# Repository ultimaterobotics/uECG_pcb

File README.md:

## uECG PCB version 4.52
 Changelog:

- Replaced AD8606 op amp with a pair of TLV271s;
- LDOs (3.3V for digital, 3V for analog side) were mixed in the previous version; strangely this didn’t affect functioning, but now this is fixed;
- Replaced BMI160 with LSM6DS3TR-C;
- Changed C6 capacitor from 2.2uF to 10uF for better low frequency performance;
- Replaced circuit protection (red LED) with diodes for more reliability;
- Changed charge resistor to 8.2K Ohm to fit the battery charging better;
- Replaced MCP71831 charger IC with TP4054; 
- Added thermistor for measuring temperature;
- Changed RGB LED to different part number;
- Added Ultimate Robotics logo on the back of the PCB.

## uECG device PCB version 4.5

PCB design in KiCAD. The main difference vs previous versions is that power is controlled via button, and slider switch is used only for long storage / shipping (and also to reset the firmware if something went really wrong).

Main project repository: https://github.com/ultimaterobotics/uECG

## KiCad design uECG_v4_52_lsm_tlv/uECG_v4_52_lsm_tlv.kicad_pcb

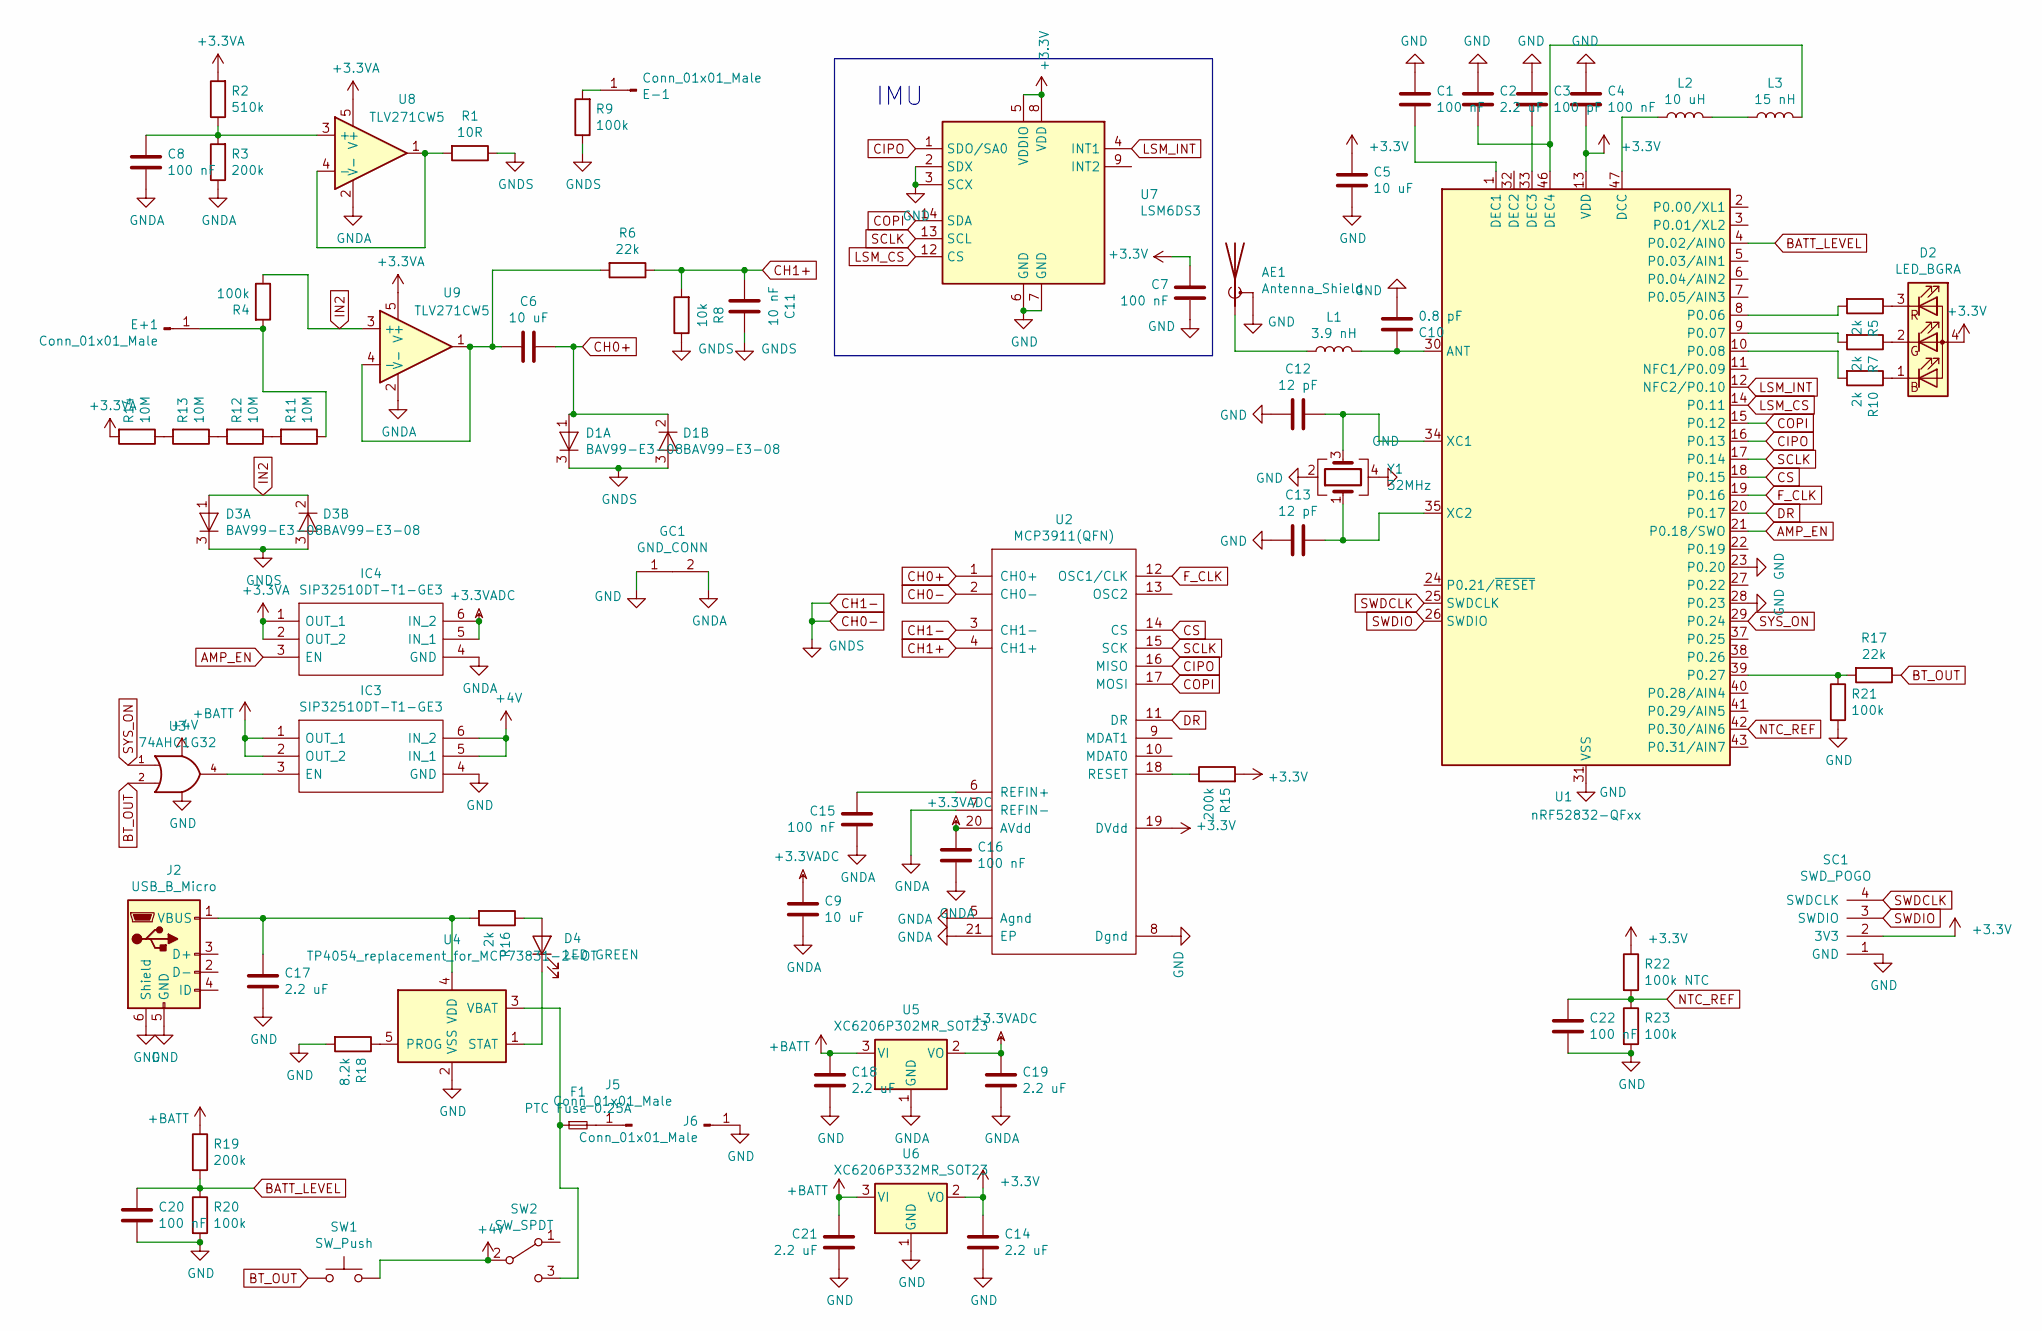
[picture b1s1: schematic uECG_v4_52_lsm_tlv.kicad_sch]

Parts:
AE1: Antenna_Shield; U.FL_Hirose_U.FL-R-SMT-1_Vertical; JLCPN C88373
C1, C4, C7, C8, C15, C16, C20, C22: 100 nF; C_0402_1005Metric; JLCPN C1525
C2, C14, C17, C18, C19, C21: 2.2 uF; C_0402_1005Metric; JLCPN C12530
C3: 100 pF; C_0402_1005Metric; JLCPN C106200
C5, C6, C9: 10 uF; C_0402_1005Metric; JLCPN C315248
C10: 0.8 pF; C_0402_1005Metric; JLCPN C88902
C11: 10 nF; C_0402_1005Metric; JLCPN C15195
C12, C13: 12 pF; C_0402_1005Metric; JLCPN C1547
D1, D3: BAV99-E3-08; SOT-23; JLCPN C2500
D2: LED_BGRA; LED_RGB_0603_a4; JLCPN C282128
D4: LED GREEN; LED_0603_1608Metric; JLCPN C72043
E+1: Conn_01x01_Male; PinHeader_1x01_P2.54mm_Vertical
E-1: Conn_01x01_Male; PinHeader_1x01_P2.54mm_Vertical
F1: PTC Fuse 0.25A; Fuse_0603_1608Metric; JLCPN C207011
GC1: GND_CONN
IC3, IC4: SIP32510DT-T1-GE3; TSOT-23-6; Manufacturer_Part_Number SIP32509DT-T1-GE3; JLCPN C145264
J2: USB_B_Micro; conn_usb_B_micro_smd_our
J5: Conn_01x01_Male; Pin_Header_Straight_1x01_Pitch2.54mm
J6: Conn_01x01_Male; PinHeader_1x01_P2.54mm_Vertical
L1: 3.9 nH; L_0402_1005Metric; JLCPN C14033
L2: 10 uH; L_0603_1608Metric; JLCPN C51942
L3: 15 nH; L_0402_1005Metric; JLCPN C27143
R1: 10R; R_0402_1005Metric; JLCPN C25077
R2: 510k; R_0402_1005Metric; JLCPN C11616
R3, R15, R19: 200k; R_0402_1005Metric; JLCPN C25764
R4, R9, R20, R21, R23: 100k; R_0402_1005Metric; JLCPN C25741
R5, R7, R10, R16: 2k; R_0402_1005Metric; JLCPN C4109
R6, R17: 22k; R_0402_1005Metric; JLCPN C25768
R8: 10k; R_0402_1005Metric; JLCPN C25744
R11, R12, R13, R14: 10М; R_0402_1005Metric; JLCPN C26082
R18: 8.2k; R_0402_1005Metric; JLCPN C25924
R22: 100k NTC; R_0402_1005Metric; JLCPN C77130
SC1: SWD_POGO
SW1: SW_Push; BTN_HY_1185
SW2: SW_SPDT; SW_SPDT_PCM12
U1: nRF52832-QFxx; QFN-48-1EP_6x6mm_Pitch0.4mm; JLCPN C77540
U2: MCP3911(QFN); QFN-20-1EP_4x4mm_P0.5mm_EP2.5x2.5mm
U3: 74AHC1G32; SOT-23-5; JLCPN C7470
U4: TP4054_replacement_for_MCP73831-2-OT; SOT-23-5; JLCPN C32574
U5: XC6206P302MR_SOT23; SOT-23; JLCPN C9972
U6: XC6206P332MR_SOT23; SOT-23; JLCPN C5446
U7: LSM6DS3; LGA-14_3x2.5mm_P0.5mm_LayoutBorder3x4y; JLCPN C967633
U8, U9: TLV271CW5; SOT-23-5; JLCPN C150498
Y1: 32MHz; Crystal_SMD_2016-4Pin_2.0x1.6mm; JLCPN C843260

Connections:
+3.3VA: IC4.1 (OUT_1), IC4.2 (OUT_2), R2.2, R14.2, U8.5 (V+), U9.5 (V+)
+3.3VADC: C9.2, C16.2, C19.2, IC4.5 (IN_1), IC4.6 (IN_2), U2.20 (AVdd), U5.2 (VO)
+3V3: C4.1, C5.2, C7.2, C14.2, D2.4 (A), R15.2, R22.1, SC1.2 (3V3), U1.13 (VDD), U1.36 (VDD), U1.48 (VDD), U2.19 (DVdd), U6.2 (VO), U7.5 (VDDIO), U7.8 (VDD)
+4V: IC3.5 (IN_1), IC3.6 (IN_2), SW1.2, SW2.2 (B), U3.5 (VCC)
+BATT: C18.2, C21.2, IC3.1 (OUT_1), IC3.2 (OUT_2), R19.1, U5.3 (VI), U6.3 (VI)
AMP_EN: IC4.3 (EN), U1.21 (P0.18/SWO)
BATT_LEVEL: C20.2, R19.2, R20.1, U1.4 (P0.02/AIN0)
BT_OUT: R17.1, SW1.1, U3.2
CH0+: C6.2, D1.1 (A), D1.2 (K), U2.1 (CH0+)
CH0-: C11.2, D1.3 (A), D3.3 (A), R1.1, R8.1, R9.1, U2.2 (CH0-), U2.3 (CH1-)
CH1+: C11.1, R6.1, R8.2, U2.4 (CH1+)
CIPO: U1.16 (P0.13), U2.16 (MISO), U7.1 (SDO/SA0)
COPI: U1.15 (P0.12), U2.17 (MOSI), U7.14 (SDA)
CS: U1.18 (P0.15), U2.14 (CS)
DR: U1.20 (P0.17), U2.11 (DR)
F_CLK: U1.19 (P0.16), U2.12 (OSC1/CLK)
GND: AE1.2 (Shield), C1.2, C2.2, C3.2, C4.2, C5.1, C7.1, C10.2, C12.1, C13.1, C14.1, C17.1, C18.1, C20.1, C21.1, C22.1, GC1.1, IC3.4 (GND), J2.5 (GND), J2.6 (Shield), J6.1, R18.2, R20.2, R21.2, R23.2, SC1.1 (GND), U1.23 (P0.20), U1.28 (P0.23), U1.31 (VSS), U1.45 (VSS), U1.49 (VSS), U2.8 (Dgnd), U3.3 (GND), U4.2 (VSS), U6.1 (GND), U7.2 (SDX), U7.3 (SCX), U7.6 (GND), U7.7 (GND), Y1.2, Y1.4
GNDA: C8.1, C9.1, C15.1, C16.1, C19.1, GC1.2, IC4.4 (GND), R3.1, U2.5 (Agnd), U2.7 (REFIN-), U2.21 (EP), U5.1 (GND), U8.2 (V-), U9.2 (V-)
IN2: D3.1 (A), D3.2 (K), R4.1, U9.3 (+)
LSM_CS: U1.14 (P0.11), U7.12 (CS)
LSM_INT: U1.12 (NFC2/P0.10), U7.4 (INT1)
NTC_REF: C22.2, R22.2, R23.1, U1.42 (P0.30/AIN6)
unnamed: AE1.1 (A), L1.1
unnamed: C1.1, U1.1 (DEC1)
unnamed: C2.1, L3.2, U1.46 (DEC4)
unnamed: C3.1, U1.33 (DEC3)
unnamed: C6.1, R6.2, U9.1, U9.4 (-)
unnamed: C8.2, R2.1, R3.2, U8.3 (+)
unnamed: C10.1, L1.2, U1.30 (ANT)
unnamed: C12.2, U1.34 (XC1), Y1.3
unnamed: C13.2, U1.35 (XC2), Y1.1
unnamed: C15.2, U2.6 (REFIN+)
unnamed: C17.2, J2.1 (VBUS), R16.2, U4.4 (VDD)
unnamed: D2.1 (BK), R10.1
unnamed: D2.2 (GK), R7.1
unnamed: D2.3 (RK), R5.1
unnamed: D4.1 (K), U4.1 (STAT)
unnamed: D4.2 (A), R16.1
unnamed: E+1.1, R4.2, R11.1
unnamed: E-1.1, R9.2
unnamed: F1.1, SW2.3 (C), U4.3 (VBAT)
unnamed: F1.2, J5.1
unnamed: IC3.3 (EN), U3.4
unnamed: L2.1, U1.47 (DCC)
unnamed: L2.2, L3.1
unnamed: R1.2, U8.1, U8.4 (-)
unnamed: R5.2, U1.8 (P0.06)
unnamed: R7.2, U1.9 (P0.07)
unnamed: R10.2, U1.10 (P0.08)
unnamed: R11.2, R12.1
unnamed: R12.2, R13.1
unnamed: R13.2, R14.1
unnamed: R15.1, U2.18 (RESET)
unnamed: R17.2, R21.1, U1.39 (P0.27)
unnamed: R18.1, U4.5 (PROG)
SCLK: U1.17 (P0.14), U2.15 (SCK), U7.13 (SCL)
SWDCLK: SC1.4 (SWDCLK), U1.25 (SWDCLK)
SWDIO: SC1.3 (SWDIO), U1.26 (SWDIO)
SYS_ON: U1.29 (P0.24), U3.1

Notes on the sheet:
IMU

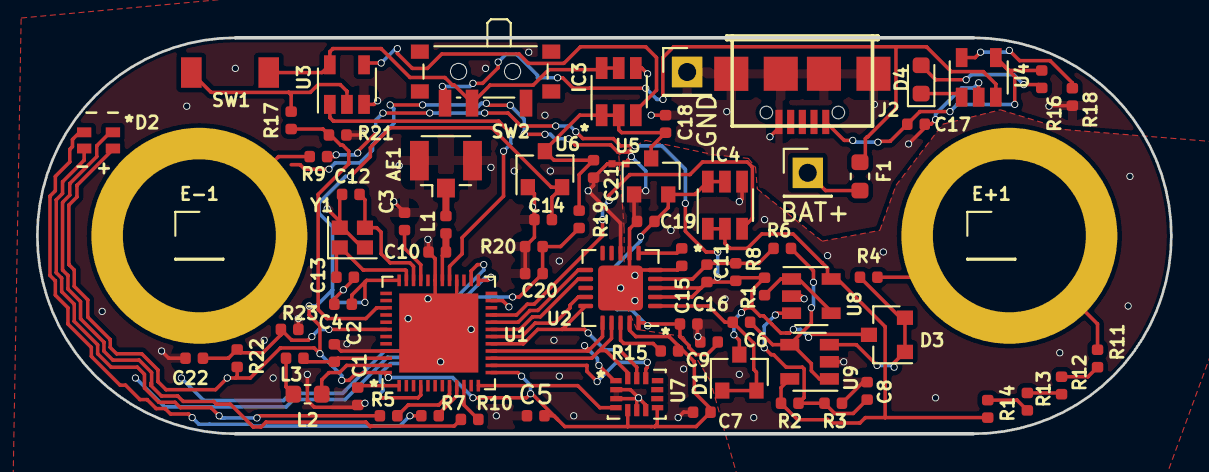
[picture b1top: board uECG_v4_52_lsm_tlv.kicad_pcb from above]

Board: 2 copper layers, 63.0 x 22.0 mm, 75 parts (1 on the bottom side), 59 nets.

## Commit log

2021-08-31 PCB design in KiCAD
2023-02-15 License changed to CERN-OHL-P instead of MIT
2023-05-29 added schematics PDF
2024-05-14 Added latest uECG version (v4_52)
    Uploaded KiCAD PCB files for v4_52
2024-05-14 Update README.md
    Added changelog for v4.52
